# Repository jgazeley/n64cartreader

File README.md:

# N64 Pico Cart Reader V2

A simple, open-source N64 cartridge reader powered by a Raspberry Pi Pico. Plug it in via USB to dump ROMs and back up saves directly to your computer using a web browser or command line.

## Features

- **Full ROM dumping** for retail N64 cartridges (up to 32 MB)
- **Save read/write/restore** for all retail save types:
  - SRAM (e.g. 1080 Snowboarding, Ocarina of Time)
  - EEPROM 4K/16K (e.g. GoldenEye, Super Mario 64)
  - FlashRAM (e.g. Majora's Mask, Pokemon Stadium)
  *(For a full list of N64 games and their save types, see [Micro-64's Game Save List](http://micro-64.com/database/gamesave.shtml))*
- **Controller Pak (MPK)** export/import
- **GameShark** cartridge export/import/restore
- **Web Serial GUI** — runs in Chrome/Edge, no install required
- **Python CLI** for all other users
- **3.3V-native design** — no level shifting needed, lower BOM cost
- **Automatic cart identification** — detects game, ROM size, and save type from a built-in catalog

## Getting Started

See [docs/GETTING_STARTED.md](docs/GETTING_STARTED.md) for full setup instructions.

### Quick Start

1. Flash the `pico_headless_demo.uf2` firmware to your Pico (hold BOOTSEL while plugging in USB, then drag the file onto the drive).
2. Insert an N64 cartridge.
3. Open the [Web Serial UI](host-tools/web/index.html) in Chrome or Edge, or use a CLI:

**Windows (PowerShell):**
```powershell
./host-tools/powershell/N64CartReader.ps1 -Port COM5
```

**Windows/macOS/Linux (Python):**
```bash
# example for windows
python3 host-tools/python/pico_pak_n64_magic_cli.py --port /dev/ttyCOM5 n64-cart-id --rescan
# example for linux
python3 host-tools/python/pico_pak_n64_magic_cli.py --port /dev/ttyACM0 n64-cart-id --rescan
```

## Project Layout

```
firmware/
  rp2040/          C-based firmware for the Raspberry Pi Pico (timing-critical bus logic)
host-tools/
  powershell/      Native CLI for Windows (no setup needed); also supports macOS/Linux
  python/          Cross-platform CLI for validation, diagnostics, and batch scripts
  web/             Easiest, driverless browser-based interface using Web Serial
hardware/
  board/           V2 hardware project (KiCad PCB, schematics, and BOM)
enclosure/
  board/           3D-printable protective case (FreeCAD and STL files)
docs/              Technical guides, hardware documentation, and troubleshooting
LICENSES/          Third-party license texts for shared components
```

## Web Serial UI

The browser-based interface is the easiest way to use the reader. It works in Chrome and Edge via the Web Serial API. No drivers or software installation required.

Open `host-tools/web/index.html` directly in your browser, click Connect, and the UI will detect your cartridge and present options for ROM dumping, save export/import, and GameShark operations.

See [docs/WEB_SERIAL_UI.md](docs/WEB_SERIAL_UI.md) for details.

## Python CLI

The Python CLI provides full access to all device capabilities and is used for bench testing, validation, and scripted workflows.

```bash
cd host-tools/python

# Identify the cartridge
python3 pico_pak_n64_magic_cli.py --port /dev/ttyACM0 n64-cart-id --rescan

# Export a save
python3 pico_pak_n64_magic_cli.py --port /dev/ttyACM0 n64-export --out my_save.bin --sha256

# Import a save with verification
python3 pico_pak_n64_magic_cli.py --port /dev/ttyACM0 n64-import --in my_save.bin --verify

# Dump the full ROM
python3 pico_pak_n64_magic_cli.py --port /dev/ttyACM0 n64-rom-dump --out my_rom.z64

# Run the validation matrix
python3 n64_validation_matrix.py --port /dev/ttyACM0
```

## PowerShell CLI

A native alternative for Windows users (no installation required). Works with the built-in PowerShell 5.1 or PowerShell 7+ (`pwsh`) on any platform. See [Getting Started](docs/GETTING_STARTED.md) for Windows execution policy setup.

```powershell
# Interactive menu (use COMx on Windows, /dev/ttyACM0 on Linux)
./host-tools/powershell/N64CartReader.ps1 -Port COM5

# Export a save
./host-tools/powershell/Export-Save.ps1 -Port COM5 -Out my_save.bin

# Import a save with verification
./host-tools/powershell/Import-Save.ps1 -Port COM5 -In my_save.bin -Verify

# Dump the full ROM
./host-tools/powershell/Dump-Rom.ps1 -Port COM5 -Out my_rom.z64
```

## Building the Firmware

Requires the [Pico SDK](https://github.com/raspberrypi/pico-sdk) and CMake.

```bash
cd firmware/rp2040
export PICO_SDK_PATH=/path/to/pico-sdk
cmake -S . -B build
cmake --build build -j4 --target pico_headless_demo
```

Flash with picotool or drag `build/pico_headless_demo.uf2` onto the Pico in BOOTSEL mode.

## Hardware

The V2 board is a single PCB with an integrated N64 cartridge slot and Raspberry Pi Pico footprint. The design is in KiCad under `hardware/board/kicad/`.

Power is supplied through USB. The RP2040 runs at 3.3V, which matches N64 cartridge logic levels directly.

Pin mapping and board documentation are in [docs/HARDWARE.md](docs/HARDWARE.md).

## Troubleshooting

**Cartridge not detected or garbled header:**
Remove the cartridge, clean the edge connector contacts with isopropyl alcohol and a cotton swab, and reseat firmly.

**EEPROM save shows `type=none` after cart swap:**
Run `n64-cart-id --rescan` or retry 3-5 times. The Joybus bus needs a moment to settle after a physical swap.

**Controller probe returns `IO_ERR`:**
EEPROM cartridges and controllers share the same Joybus data line. Unplug one to test the other.

**Web Serial won't connect:**
Web Serial requires Chrome or Edge. Firefox and Safari are not supported. Make sure no other application (terminal, serial monitor) has the port open.

## V1 Legacy

The original N64 Cart Reader was built on an Arduino Mega 2560 with an SD card for storage and a serial terminal interface. That design is preserved in the `legacy/v1-arduino` branch.

See [docs/V1_LEGACY.md](docs/V1_LEGACY.md) for details on the original hardware.

## Acknowledgements

N64 Pico Cart Reader V2 was designed and implemented by Jayson Gazeley as an RP2040-based successor to the original Arduino N64 Cart Reader.

The project builds on prior open-source preservation work, especially:

- **[Sanni Cart Reader](https://github.com/sanni/cartreader)** (GPL-3.0) — foundational N64 cartridge interfacing logic
- **[drmdmp64_mass / DreamDumper64](https://github.com/nopjne/drmdmp64_mass)** by nopjne (BSD-2-Clause) — Joybus PIO and EEPROM reference implementation
- **skaman** — multi-console cart-reader modules
- **hkz & themanbehindthecurtain** — FlashRAM command documentation
- **Andrew Brown & Peter Den Hartog** — N64 controller protocol
- **libdragon** — N64 controller checksums

See [docs/CREDITS_AND_PRIOR_ART.md](docs/CREDITS_AND_PRIOR_ART.md) for full attribution and [docs/LICENSING.md](docs/LICENSING.md) for license details.

## References

- [Joybus Protocol](https://n64brew.dev/wiki/Joybus_Protocol)
- [N64 Hardware Architecture](https://www.copetti.org/writings/consoles/nintendo-64/)

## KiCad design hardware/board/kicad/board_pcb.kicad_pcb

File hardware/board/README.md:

# N64 Pico Cart Reader V2 Hardware

This directory contains the custom KiCad PCB design files and fabrication outputs for the N64 Pico Cart Reader V2.

## Directory Structure

- **`docs/`**: Hardware documentation, including the current `PINMAP.md` that outlines the routing between the Raspberry Pi Pico and the N64 cartridge slot.
- **`kicad/`**: The complete, editable KiCad project (`.kicad_pro`, `.kicad_sch`, `.kicad_pcb`).
  - **`lib/`**: Custom project symbols and footprints (e.g., the N64 cartridge slot footprint).
- **`fabrication/`**: Board manufacturing outputs.
  - **`jlcpcb/`**: A known-good `.zip` file containing the Gerbers and drill files formatted and ready for upload to JLCPCB.
  - **`gerbers/`**: The individual, extracted Gerber and drill files.

## Hardware Quirk: EEPROM Latency
When testing the hardware, note that after a physical cartridge swap, the initial Joybus detection may return `type=none` for EEPROM saves. This is a known hardware limitation. It typically requires 3-5 retries or an explicit software rescan to allow the bus to settle.

## Licensing
The hardware design files (schematics, PCB layouts, custom footprints) are released under the [Creative Commons Attribution 4.0 International (CC BY 4.0)](https://creativecommons.org/licenses/by/4.0/) license. This license was chosen to maintain continuity with the hardware licensing of the original V1 Arduino-based project from which this work conceptually descends.

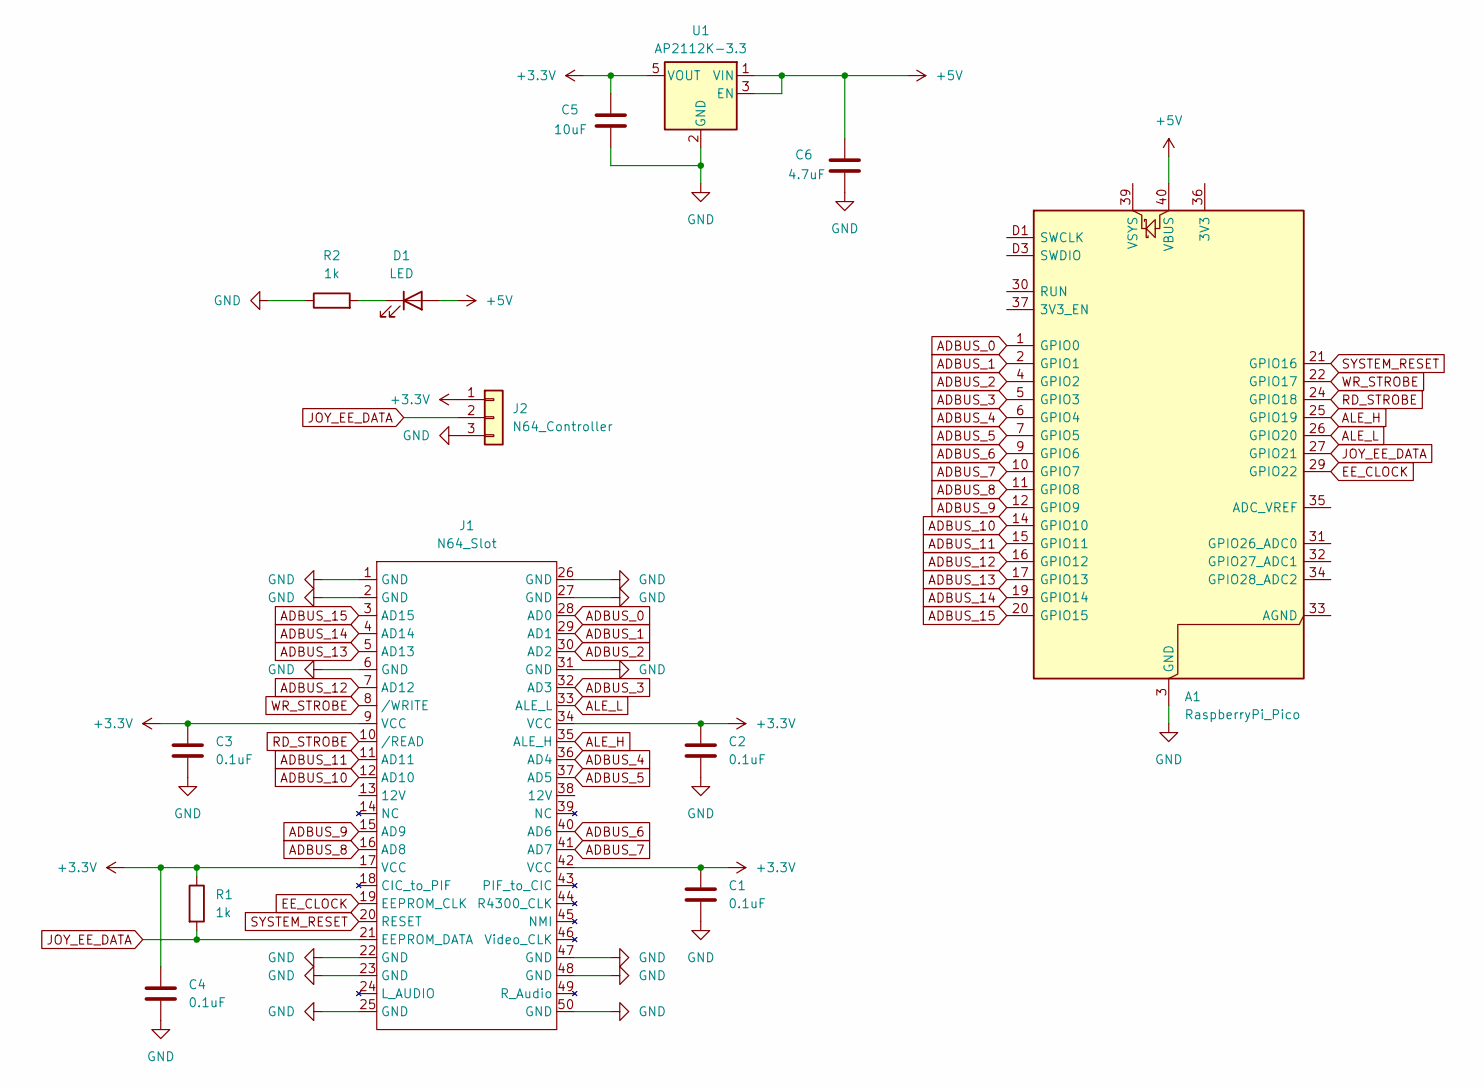
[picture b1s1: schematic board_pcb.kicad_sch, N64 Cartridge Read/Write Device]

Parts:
A1: RaspberryPi_Pico; RaspberryPi_Pico_SMD
C1, C2, C3, C4: 0.1uF; C_0805_2012Metric_Pad1.18x1.45mm_HandSolder
C5: 10uF; C_0805_2012Metric_Pad1.18x1.45mm_HandSolder
C6: 4.7uF; C_0805_2012Metric_Pad1.18x1.45mm_HandSolder
D1: LED; LED_D3.0mm
J1: N64_Slot
J2: N64_Controller; Controller_Port_3Pin
R1, R2: 1k; R_Axial_DIN0207_L6.3mm_D2.5mm_P10.16mm_Horizontal
U1: AP2112K-3.3; SOT-23-5

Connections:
+3.3V: C1.1, C2.1, C3.1, C4.1, C5.1, J1.9 (VCC), J1.17 (VCC), J1.34 (VCC), J1.42 (VCC), J2.1, R1.1, U1.5 (VOUT)
+5V: A1.40 (VBUS), C6.1, D1.2 (A), U1.1 (VIN), U1.3 (EN)
ADBUS_0: A1.1 (GPIO0), J1.28 (AD0)
ADBUS_1: A1.2 (GPIO1), J1.29 (AD1)
ADBUS_2: A1.4 (GPIO2), J1.30 (AD2)
ADBUS_3: A1.5 (GPIO3), J1.32 (AD3)
ADBUS_4: A1.6 (GPIO4), J1.36 (AD4)
ADBUS_5: A1.7 (GPIO5), J1.37 (AD5)
ADBUS_6: A1.9 (GPIO6), J1.40 (AD6)
ADBUS_7: A1.10 (GPIO7), J1.41 (AD7)
ADBUS_8: A1.11 (GPIO8), J1.16 (AD8)
ADBUS_9: A1.12 (GPIO9), J1.15 (AD9)
ADBUS_10: A1.14 (GPIO10), J1.12 (AD10)
ADBUS_11: A1.15 (GPIO11), J1.11 (AD11)
ADBUS_12: A1.16 (GPIO12), J1.7 (AD12)
ADBUS_13: A1.17 (GPIO13), J1.5 (AD13)
ADBUS_14: A1.19 (GPIO14), J1.4 (AD14)
ADBUS_15: A1.20 (GPIO15), J1.3 (AD15)
ALE_H: A1.25 (GPIO19), J1.35 (ALE_H)
ALE_L: A1.26 (GPIO20), J1.33 (ALE_L)
EE_CLOCK: A1.29 (GPIO22), J1.19 (EEPROM_CLK)
GND: A1.3 (GND), A1.8 (GND), A1.13 (GND), A1.18 (GND), A1.23 (GND), A1.28 (GND), A1.38 (GND), A1.D2 (GND), C1.2, C2.2, C3.2, C4.2, C5.2, C6.2, J1.1 (GND), J1.2 (GND), J1.6 (GND), J1.22 (GND), J1.23 (GND), J1.25 (GND), J1.26 (GND), J1.27 (GND), J1.31 (GND), J1.47 (GND), J1.48 (GND), J1.50 (GND), J2.3, R2.1, U1.2 (GND)
JOY_EE_DATA: A1.27 (GPIO21), J1.21 (EEPROM_DATA), J2.2, R1.2
unnamed: D1.1 (K), R2.2
RD_STROBE: A1.24 (GPIO18), J1.10 (/READ)
SYSTEM_RESET: A1.21 (GPIO16), J1.20 (RESET)
WR_STROBE: A1.22 (GPIO17), J1.8 (/WRITE)

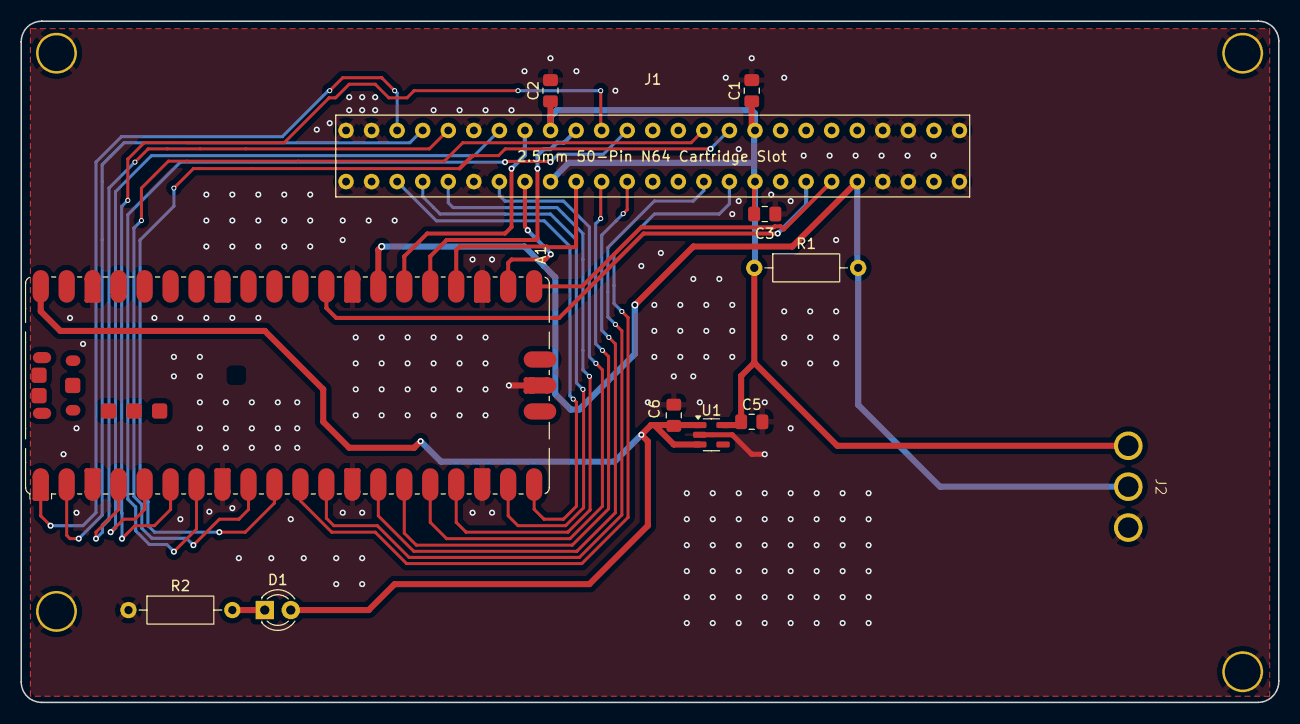
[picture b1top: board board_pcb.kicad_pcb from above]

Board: 2 copper layers, 123.0 x 66.6 mm, 12 parts (0 on the bottom side), 27 nets.

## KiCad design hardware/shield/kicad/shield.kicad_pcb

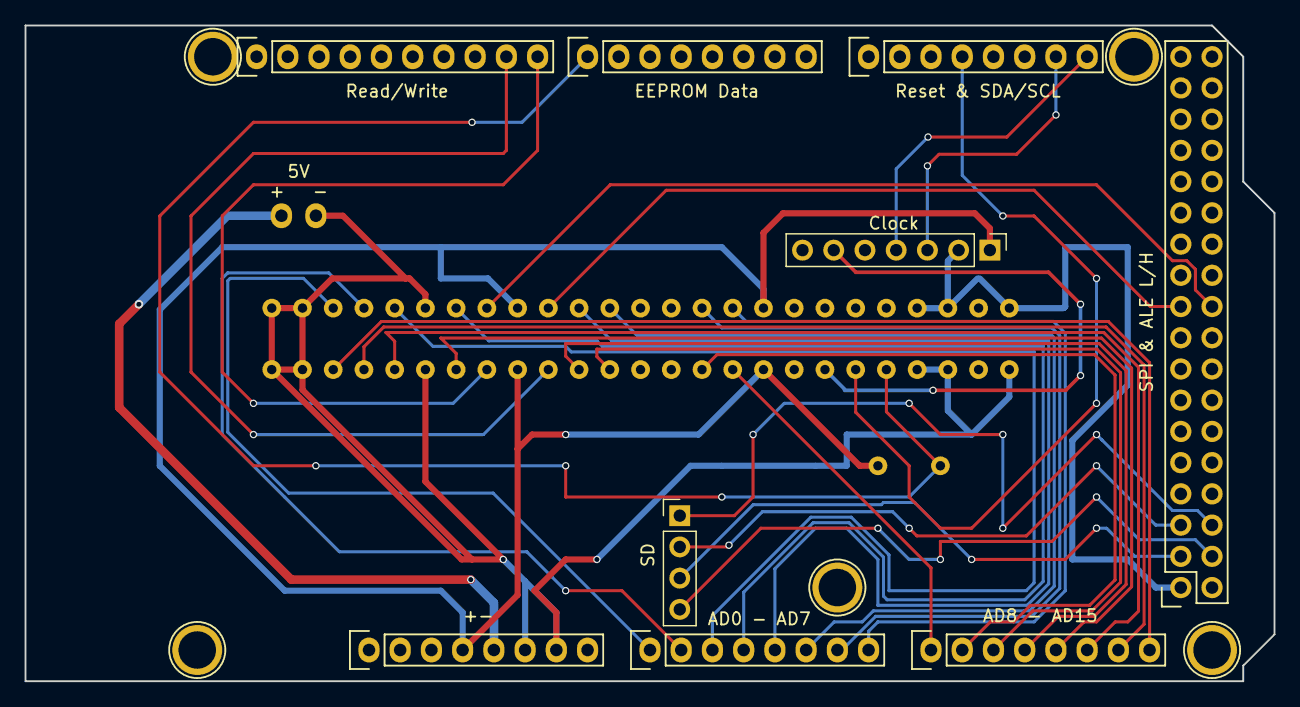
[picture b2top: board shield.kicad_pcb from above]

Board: 2 copper layers, 101.6 x 53.3 mm, 15 parts (0 on the bottom side), 32 nets.

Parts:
+-: Power; Socket_Strip_Arduino_1x08
AD0 - AD7, AD8 - AD15: Analog; Socket_Strip_Arduino_1x08
Clock: PinHeader_1x07_P2.54mm_Vertical
EEPROM Data: PWM; Socket_Strip_Arduino_1x08
J1: N64_Slot; N64 Slot
P8, P9, P10, P11, P13: CONN_01X01; Arduino_1pin
Read/Write: PWM; Socket_Strip_Arduino_1x10
Reset & SDA/SCL: Communication; Socket_Strip_Arduino_1x08
SD: PinHeader_1x04_P2.54mm_Vertical
SPI & ALE L/H: Digital; Socket_Strip_Arduino_2x18

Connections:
+3V3: +-.4, Clock.1, J1.9 (VCC), J1.17 (VCC), J1.34 (VCC), J1.42 (VCC)
+5V: +-.5, SPI & ALE L/H.35, SPI & ALE L/H.36
/7(**): EEPROM Data.7, J1.21 (EEPROM_DATA)
/8(**): J1.8 (/WRITE), Read/Write.8
/9(**): J1.10 (/READ), Read/Write.9
/16(Tx2): Clock.6, J1.19 (EEPROM_CLK), Reset & SDA/SCL.16
/17(Rx2): J1.20 (RESET), Reset & SDA/SCL.17
/20(SDA): Clock.3, Reset & SDA/SCL.20
/21(SCL): Clock.4, Reset & SDA/SCL.21
/36: J1.35 (ALE_H), SPI & ALE L/H.36
/37: J1.33 (ALE_L), SPI & ALE L/H.37
/50(MISO): SD.2, SPI & ALE L/H.5
/51(MOSI): SD.1, SPI & ALE L/H.6
/52(SCK): SD.3, SPI & ALE L/H.3
/53(SS): SD.4, SPI & ALE L/H.4
/A0: AD0 - AD7.1, J1.28 (AD0)
/A1: AD0 - AD7.2, J1.29 (AD1)
/A2: AD0 - AD7.3, J1.30 (AD2)
/A3: AD0 - AD7.4, J1.32 (AD3)
/A4: AD0 - AD7.5, J1.36 (AD4)
/A5: AD0 - AD7.6, J1.37 (AD5)
/A6: AD0 - AD7.7, J1.40 (AD6)
/A7: AD0 - AD7.8, J1.41 (AD7)
/A8: AD8 - AD15.1, J1.16 (AD8)
/A9: AD8 - AD15.2, J1.15 (AD9)
/A10: AD8 - AD15.3, J1.12 (AD10)
/A11: AD8 - AD15.4, J1.11 (AD11)
/A12: AD8 - AD15.5, J1.7 (AD12)
/A13: AD8 - AD15.6, J1.5 (AD13)
/A14: AD8 - AD15.7, J1.4 (AD14)
/A15: AD8 - AD15.8, J1.3 (AD15)
GND: +-.6, +-.7, Clock.2, J1.1 (GND), J1.2 (GND), J1.6 (GND), J1.22 (GND), J1.23 (GND), J1.25 (GND), J1.26 (GND), J1.27 (GND), J1.31 (GND), J1.47 (GND), J1.48 (GND), J1.50 (GND), Read/Write.4, SPI & ALE L/H.1, SPI & ALE L/H.2

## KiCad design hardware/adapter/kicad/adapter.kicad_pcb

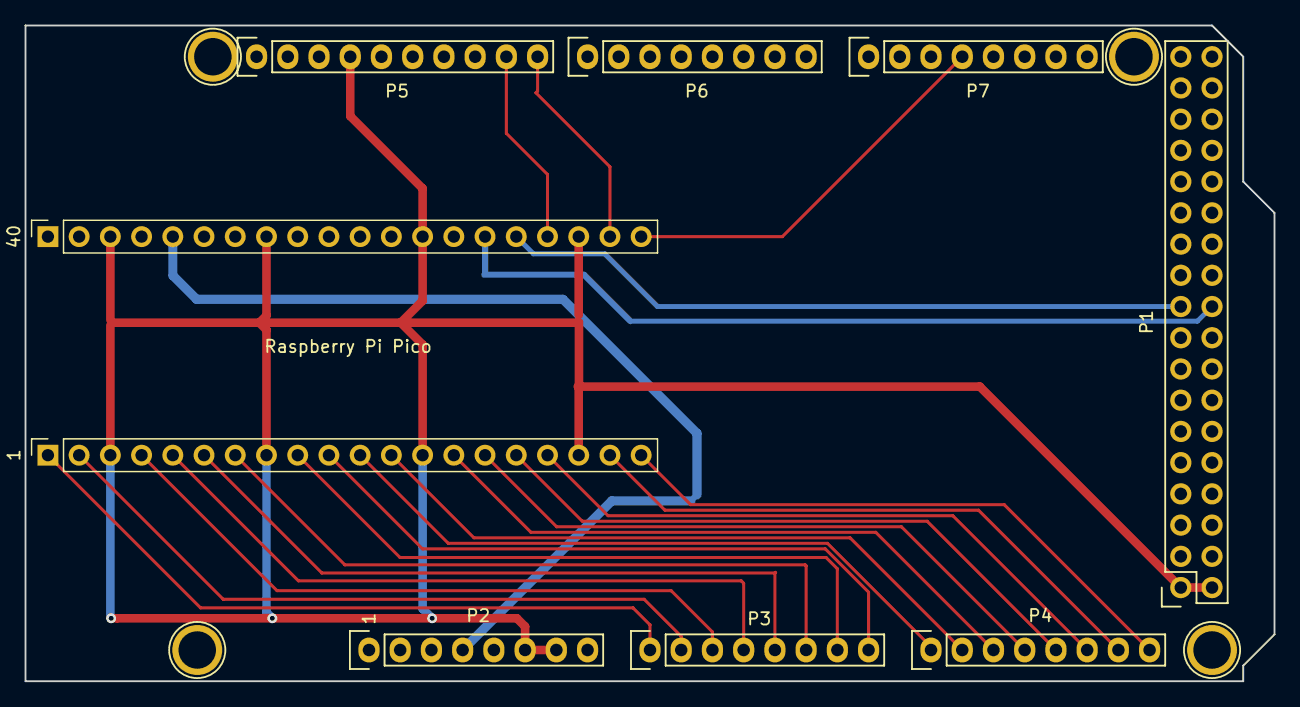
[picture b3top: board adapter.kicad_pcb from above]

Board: 2 copper layers, 101.6 x 53.3 mm, 13 parts (0 on the bottom side), 24 nets.

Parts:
1, 40: PinSocket_1x20_P2.54mm_Vertical
P1: ALE H/L; Socket_Strip_Arduino_2x18
P2: Power; Socket_Strip_Arduino_1x08
P3, P4: AD Bus; Socket_Strip_Arduino_1x08
P5: Read / Write; Socket_Strip_Arduino_1x10
P6: None; Socket_Strip_Arduino_1x08
P7: Reset / Clock; Socket_Strip_Arduino_1x08
P8, P10, P11, P13: CONN_01X01; Arduino_1pin

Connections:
+3V3: 40.5, P2.4
+5V: 40.1, P1.35, P1.36, P2.5
/8(**): 40.GPIO17, P5.WRITE
/9(**): 40.GPIO18, P5.READ
/36: 40.GPIO19, P1.36
/37: 40.GPIO20, P1.37
/A0: 1.1, P3.1
/A1: 1.2, P3.2
/A2: 1.4, P3.3
/A3: 1.5, P3.4
/A4: 1.6, P3.5
/A5: 1.7, P3.6
/A6: 1.9, P3.7
/A7: 1.10, P3.8
/A8: 1.11, P4.1
/A9: 1.12, P4.2
/A10: 1.14, P4.3
/A11: 1.15, P4.4
/A12: 1.16, P4.5
/A13: 1.17, P4.6
/A14: 1.19, P4.7
/A15: 1.20, P4.8
/Reset: 40.GPIO16, P2.3, P7.17
GND: 1.3, 1.8, 1.13, 1.18, 40.3, 40.8, 40.13, 40.18, P1.1, P1.2, P2.6, P2.7, P5.4

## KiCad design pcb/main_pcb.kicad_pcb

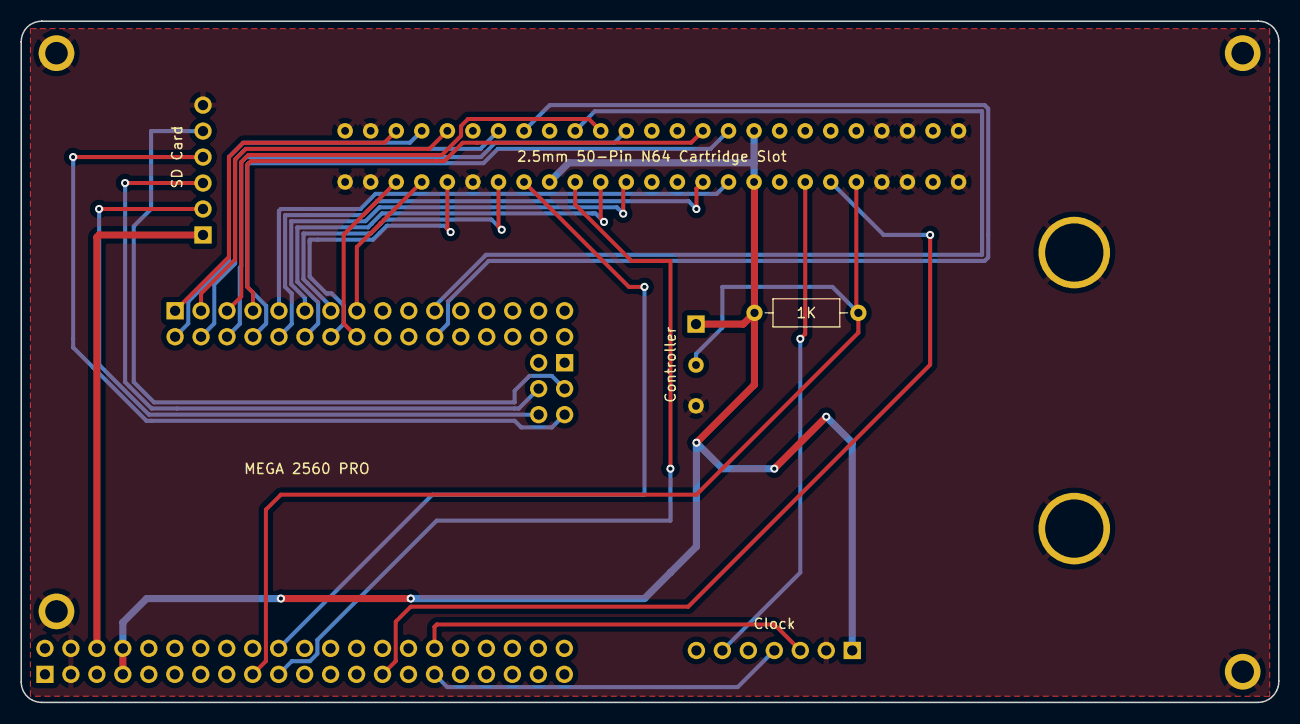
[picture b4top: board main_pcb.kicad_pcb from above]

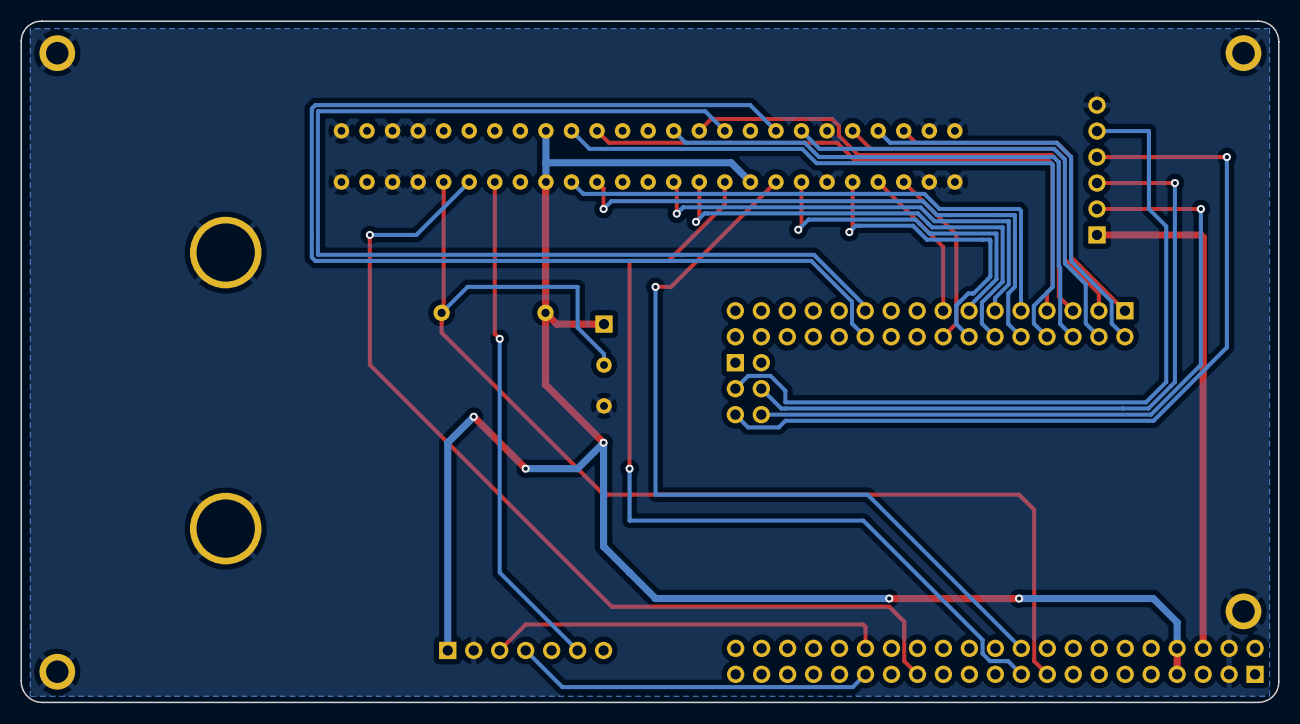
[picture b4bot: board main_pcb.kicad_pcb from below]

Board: 2 copper layers, 123.0 x 66.6 mm, 7 parts (3 on the bottom side), 32 nets.

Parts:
Clock: 01x07; PinHeader_1x07_P2.54mm_Vertical
J1: N64_Slot; N64 Slot
J1#2: MEGA BOTTOM; PinSocket_2x21_P2.54mm_Vertical
J2: MEGA TOP; PinSocket_2x16_P2.54mm_Vertical
J5: MEGA SIDE; PinSocket_2x03_P2.54mm_Vertical
R1: 1K; R_Axial_DIN0207_L6.3mm_D2.5mm_P10.16mm_Horizontal
SD Card: 01x06; PinHeader_1x06_P2.54mm_Vertical

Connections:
+3V3: Clock.VIN, J1.9 (VCC), J1.17 (VCC), J1.34 (VCC), J1.42 (VCC), J1#2.35, J1#2.36, R1.1
+5V: J1#2.37, J1#2.38, SD Card.1
A0: J1.28 (AD0), J2.31
A1: J1.29 (AD1), J2.32
A2: J1.30 (AD2), J2.29
A3: J1.32 (AD3), J2.30
A4: J1.36 (AD4), J2.27
A5: J1.37 (AD5), J2.28
A6: J1.40 (AD6), J2.25
A7: J1.41 (AD7), J2.26
A8: J1.16 (AD8), J2.23
A9: J1.15 (AD9), J2.24
A10: J1.12 (AD10), J2.21
A11: J1.11 (AD11), J2.22
A12: J1.7 (AD12), J2.19
A13: J1.5 (AD13), J2.20
A14: J1.4 (AD14), J2.17
A15: J1.3 (AD15), J2.18
CLK1: Clock.1, J1.19 (EEPROM_CLK)
D7: J1.21 (EEPROM_DATA), J1#2.26, R1.2
D8: J1.8 (/WRITE), J1#2.23
D9: J1.10 (/READ), J1#2.24
D17: J1.20 (RESET), J1#2.16
D20: Clock.SDA, J1#2.11
D21: Clock.SCL, J1#2.12
D36: J1.35 (ALE_H), J2.11
D37: J1.33 (ALE_L), J2.12
D50: J5.4, SD Card.5
D51: J5.3, SD Card.3
D52: J5.6, SD Card.4
D53: J5.5, SD Card.2
GND: Clock.GND, J1.1 (GND), J1.2 (GND), J1.6 (GND), J1.22 (GND), J1.23 (GND), J1.25 (GND), J1.26 (GND), J1.27 (GND), J1.31 (GND), J1.47 (GND), J1.48 (GND), J1.50 (GND), J1#2.39, J1#2.40, SD Card.6

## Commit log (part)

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2025-06-19 Rename n64cartreader.txt
2025-06-19 Refactor project structure
2025-06-19 Update firmware
2025-06-23 rp2040 with CLI + parallel & serial bus
2025-06-23 Move atmega2560 to subfolder
2025-06-26 feat: Completely reimplemented RP2040 firmware for N64 Cart Reader.
    This commit replaces the previous RP2040 firmware with a ground-up
    reimplementation, focusing on modularity and testability.
    **Key Changes/Features:**
    - New architecture for [mention high-level architectural changes, e.g., improved state machine, clearer module separation].
    - Integration of core modules like [list examples: e.g., redesigned ADbus, streamlined Joybus PIO].
    - Framework for future expansion with [e.g., dedicated device handlers, flexible CLI commands].
2025-07-04 MSC working, TODO: Fix flash writes; corrupt from 0x4005 to 0x407F
2025-07-07 TODO: Fix flash writes; from 0x4000 to EOF
2026-03-03 Snapshot of firmware after migration from Windows to Debian, presumed working but about to replace with newer working version. (pico-pak)
2026-03-03 Snapshot of working firmware with all 3 save types working for read AND write, ROM dump working
2026-04-11 V2 launch: integrated repo with docs, cleanup, and validation
    - Firmware: RP2040 headless firmware with GameShark and utils support
    - Host tools: Python CLI, validation matrix, Web Serial UI
    - Hardware: V2 KiCad project with gerbers, fabrication outputs, custom footprint library
    - Enclosure: FreeCAD source and STL for V2 board case
    - Docs: README, GETTING_STARTED, HARDWARE, WEB_SERIAL_UI, V1_LEGACY,
    CREDITS_AND_PRIOR_ART, KNOWN_LIMITATIONS, LICENSING, VALIDATION,
2026-04-11 Fix firmware build version tag
2026-04-11 Fix host CLI build tag
2026-04-12 Use cart-independent MPK export filenames
2026-04-12 Improve Python CLI serial port selection
2026-04-12 Clarify Web UI catalog loading behavior
2026-04-12 Simplify Web UI catalog loading
2026-04-12 Bundle Web UI catalog for file mode
2026-04-12 Clarify Joybus data pin naming
2026-04-12 Clean up public documentation
2026-04-12 Experimental: Open-drain Joybus PIO and repro EEPROM diagnostics
2026-04-13 Add PowerShell host tool and bump ROM export chunk size
    PowerShell CLI for N64 cart operations (dump ROM, export/import saves)
    with zero external dependencies — works with built-in PowerShell 5.1 on
    Windows or PowerShell 7+ on any platform. Tested on Linux against
    FlashRAM, SRAM, and EEPROM carts with byte-identical results to the
    Python CLI.
    Also increases ROM export chunk from 512 to 2048 bytes for faster dumps,
2026-04-13 Revert ROM export chunk size to 512 bytes to fix corruption on large ROMs
2026-04-13 Update docs with platform-specific CLI examples for Windows and Linux
2026-04-13 Refine project layout and PowerShell descriptions for clarity
2026-04-13 Refine documentation hierarchy: Web UI as easiest, PowerShell as native Windows CLI
